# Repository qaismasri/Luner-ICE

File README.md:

<div align="center">

# Lunar-ICE Rover

**A remotely operated lunar rover that drives a simulated lunar surface and identifies rocks
by their radio, infrared, ultrasonic and magnetic signatures.**

Imperial College London · ELEC40006 Electronics Design Project 1 (EEERover) · Group 15

</div>

## About the project

The goal was to design and build, from scratch, a remotely controlled rover capable of exploring a simulated lunar surface and surveying the rocks it finds there. The rover has to be driven around large obstacles by a remote operator, park itself next to a target rock, and work out two things about it: **how old it is**, and **what type of rock it is**.

Nothing about the rock is visible from the outside. Everything the rover reports has to be recovered from four faint signals the rock emits — a radio transmission carrying its age, infrared pulses, an ultrasonic tone, and a magnetic field. Each of those needed its own sensor, its own analogue signal chain to pull a usable signal out of the noise, and its own place on the chassis.

The project ran over one term as a six-person group design exercise, and had to satisfy a handful of hard constraints:

- **Under 750 g** all-up mass
- **£60 budget** for components
- **3.3 V logic throughout** — the microcontroller's inputs are not 5 V tolerant
- Driven entirely by a **remote operator**, with no line-of-sight assumptions beyond the same Wi-Fi network

<div align="center">
<table>
<tr>
<td width="50%" align="center" valign="top">

<br><sub><b>Complete assembly</b> — both plates, radio arm and sensor arm</sub>
</td>
<td width="50%" align="center" valign="top">

<br><sub><b>Two-plate stack</b> — motors and power below, sensors above</sub>
</td>
</tr>
<tr>
<td width="50%" align="center" valign="top">

<br><sub><b>Sensor arm</b> — sweeps three sensors across the rock</sub>
</td>
<td width="50%" align="center" valign="top">

<br><sub><b>Radio arm</b> — fixed, angled down toward the rock</sub>
</td>
</tr>
</table>
</div>

> These are the Fusion 360 renders. Photographs of the built rover are the one thing this repository still lacks — see [the wanted list](docs/images/README.md#photographs-still-wanted).

<div align="right"></div>

## Contents

| Section | What you will find |
|:---|:---|
| **[About the project](#about-the-project)** | Goals, constraints and what the rover has to do |
| **[Team](#team)** | Who built it, and who did what |
| **[The sensors](#the-sensors)** | The four sensing subsystems, one picture each |
| **[Identifying a rock](#identifying-a-rock)** | How four signals become a rock type and an age |
| **[System architecture](#system-architecture)** | The two-board split and how data flows |
| **[Documentation](#documentation)** | All twelve technical chapters |
| **[Repository layout](#repository-layout)** | Where everything lives |
| **[Build and run](#build-and-run)** | Getting it onto the hardware |

For the full technical write-up — calculations, simulations, measurements and PCB files — go to **[the documentation](docs/README.md)**.

<div align="right"></div>

## Team

**Group 15** — six first-year students, with the work split by subsystem.

| Name | Main contributions |
|:---|:---|
| **Tibor Varga** | Radio circuit design and LTspice simulation |
| **Junhao Liu** | Chassis and sensor arm CAD, magnetic sensing |
| **Qais Masri** | Radio research, PCB design, movement and controller, finances |
| **Tunir Sarkar** | Infrared sensor and firmware |
| **Yangping Li** | Motor subsystem and drive integration |
| **Shivang Mehra** | Ultrasound and magnetic sensing, integration |

<div align="right"></div>

## The sensors

Four independent subsystems. The **radio** reports the rock's age; the other three combine to give its type.

<table>
<tr>
<td width="50%" align="center" valign="top">

<br><b>Radio</b> · rock age
<br><sub>120-turn ferrite coil tuned to 89&nbsp;kHz.<br>ASK carrier, UART at 600&nbsp;baud.</sub>
</td>
<td width="50%" align="center" valign="top">

<br><b>Infrared</b> · rock type
<br><sub>SFH300 phototransistor, ×100 amplifier,<br>band-pass filter, LM393 comparator.</sub>
</td>
</tr>
<tr>
<td width="50%" align="center" valign="top">

<br><b>Ultrasound</b> · rock type
<br><sub>Prowave 400SR160 receiver, two ×34 stages,<br>deliberately clipped, envelope detected.</sub>
</td>
<td width="50%" align="center" valign="top">

<br><b>Magnetic</b> · rock type
<br><sub>SEN0619 (BMM350) TMR magnetometer,<br>0.1&nbsp;µT resolution over I²C.</sub>
</td>
</tr>
</table>

Click any sensor to read its full design write-up.

<div align="right"></div>

## Identifying a rock

Each rock type maps to a unique combination of the three type-sensors:

| Rock type | Infrared | Ultrasound | Magnetic |
|:---|:---|:---|:---|
| **Basaltoid** | 547 Hz | Present | Down |
| **Gravion** | 312 Hz | Absent | Down |
| **Regolix** | 312 Hz | Present | Up |
| **Lunarite** | 547 Hz | Absent | Up |

Read as a truth table, any **two** of the three columns identify all four types. All three are measured anyway, so they cross-check one another and produce a **confidence score** — the figure that tells the operator when a reading is unreliable and should be rescanned.

The rover is driven and scanned entirely from a browser on the same Wi-Fi network, so the operator needs no special software.

<div align="center">

</div>

<div align="right"></div>

## System architecture

The rover runs on **two Adafruit Metro M0 Express boards**, split by responsibility. Board 2 does nothing but read sensors; Board 1 handles Wi-Fi, the motors and the classification. Keeping them separate means network activity can never disturb sensor timing.

```mermaid
flowchart LR
    subgraph Rock
        R["Target rock"]
    end

    subgraph B2["Board 2 — Sensing"]
        RAD["Radio<br/>89 kHz ASK"]
        IR["Infrared<br/>pulse counter"]
        US["Ultrasound<br/>40 kHz"]
        MAG["Magnetometer<br/>BMM350"]
    end

    subgraph B1["Board 1 — Control"]
        WEB["Wi-Fi web server"]
        CLS["Classification"]
        MOT["Motor driver"]
    end

    OP(["Operator<br/>browser + gamepad"])

    R --> RAD & IR & US & MAG
    RAD & IR & US & MAG --> PKT["Sensor packet @ 1 Hz"]
    PKT -->|"UART link"| B1
    WEB <-->|HTTP over Wi-Fi| OP
    CLS --> WEB
    MOT --> WHEELS["Drive motors"]
```

<div align="center">

</div>

<div align="right"></div>

## Documentation

The complete write-up — design reasoning, calculations, LTspice simulations, oscilloscope captures, CAD renders and PCB layouts — lives in [`docs/`](docs/README.md).

| # | Chapter | What it covers |
|:--|:---|:---|
| 01 | [System overview](docs/01-system-overview.md) | Mission objectives, rock types, architecture, data flow |
| 02 | [Infrared sensing](docs/02-infrared.md) | Phototransistor front-end, band-pass filtering, comparator, pulse counting |
| 03 | [Radio sensing](docs/03-radio.md) | Ferrite antenna, tuned LC, amplifier, envelope detector, Schmitt trigger, UART decode |
| 04 | [Ultrasound sensing](docs/04-ultrasound.md) | 40 kHz transducer, two-stage gain, deliberate clipping, envelope detection |
| 05 | [Magnetic field sensing](docs/05-magnetic-field.md) | Hall-effect dead end, switch to a TMR magnetometer, thresholds |
| 06 | [Mechanical design](docs/06-mechanical-design.md) | Two-plate chassis, radio arm, servo-driven sensor sweep arm |
| 07 | [Movement and control](docs/07-movement-and-control.md) | Tank steering, keyboard control, gamepad mixing, latency fix |
| 08 | [PCB design](docs/08-pcb-design.md) | Two-board split, schematics, footprints, layout rules |
| 09 | [Web interface](docs/09-web-interface.md) | Mission control page, chunked serving, scan workflow |
| 10 | [Dual-board architecture](docs/10-dual-board-architecture.md) | Why two boards, the UART link, packet format, classification |
| 11 | [Cost and bill of materials](docs/11-cost-and-bom.md) | Component spend against budget |
| 12 | [References](docs/12-references.md) | Datasheets and sources |

New to the project? Start with [chapter 01](docs/01-system-overview.md).

<div align="right"></div>

## Repository layout

```
Lunar-ICE/
├── docs/                      Technical documentation and all 71 figures
│
├── Full_Board_Code/           Flight firmware — the code that runs on the rover
│   ├── Board 1/               Wi-Fi, web server, motors, rock classification
│   └── Board 2/               All four sensors, streams readings to Board 1
│
├── Lonely_Board/              Single-board prototype (everything on one Metro M0)
│
├── sensing/                   Per-subsystem research, test firmware and PCBs
│   ├── Infrared/              IR pulse-detection test code
│   ├── radio/                 Coil calculations and radio test code
│   ├── ultrasonic/            Ultrasonic test code and design notes
│   ├── magnetic/              Magnetometer test code
│   └── PCBs/                  KiCad projects and manufacturing Gerbers
│
└── software/                  Web interface, servo tests, classification notes
    ├── Website/rover_website/ Board 1 firmware serving mission control
    └── Servo_test/            Sensor-arm servo sweep test
```

Every folder has its own README: [docs](docs/README.md) · [figures](docs/images/README.md) · [firmware](Full_Board_Code/README.md) · [prototype](Lonely_Board/README.md) · [sensing](sensing/README.md) · [software](software/README.md)

<div align="right"></div>

## Build and run

You will need [PlatformIO](https://platformio.org/install) and two Adafruit Metro M0 Express boards, one with a WINC1500 Wi-Fi shield.

```bash
cd "Full_Board_Code/Board 1"     # Wi-Fi, web interface, motors, classification
pio run --target upload

cd "Full_Board_Code/Board 2"     # sensors
pio run --target upload
```

Board 1 prints its IP address over USB serial on boot — open it in a browser on the same network to drive the rover and trigger scans.

Wiring, Wi-Fi credentials and build notes are in **[Full_Board_Code/README.md](Full_Board_Code/README.md)**.

<div align="right"></div>

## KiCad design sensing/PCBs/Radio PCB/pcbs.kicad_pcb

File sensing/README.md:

[← Repo home](../README.md) · [Technical documentation](../docs/README.md)

# Sensing

Research, circuit design, test firmware and PCB files for all four sensing subsystems on the Lunar-ICE rover.

Each subsystem detects one property of a rock and reduces it to a signal the Metro M0 can read. The full write-up for each — design reasoning, calculations, simulations and measurements — is in [`docs/`](../docs/); this folder holds the working files.

---

## Subsystems

| Subsystem | Detects | Documentation | Test firmware | Status |
|---|---|---|---|---|
| **Radio** | Rock age, via 89 kHz ASK | [docs/03-radio.md](../docs/03-radio.md) | [`radio/radio_test_code/`](radio/radio_test_code/) | ✅ Working |
| **Infrared** | Rock type, via pulse rate | [docs/02-infrared.md](../docs/02-infrared.md) | [`Infrared/ir_test_code/`](Infrared/ir_test_code/) | ✅ Working |
| **Ultrasound** | Rock type, via 40 kHz tone | [docs/04-ultrasound.md](../docs/04-ultrasound.md) | [`ultrasonic/ultrasonic_test_code/`](ultrasonic/ultrasonic_test_code/) | ✅ Working |
| **Magnetic** | Rock type, via magnet polarity | [docs/05-magnetic-field.md](../docs/05-magnetic-field.md) | [`magnetic/Magnetic_test_code/`](magnetic/Magnetic_test_code/) | ✅ Working |

---

## Folder contents

```
sensing/
├── Infrared/
│   └── ir_test_code/                  Pulse counting via hardware interrupt
├── radio/
│   ├── COIL_CALCULATIONS.md           Ferrite coil inductance and resistance working
│   ├── step1_coil_antenna.png         The wound coil
│   └── radio_test_code/               UART decode of the demodulated bitstream
├── ultrasonic/
│   ├── Ultrasonic_sensor_notes.md     Transducer, gain planning and test log
│   └── ultrasonic_test_code/          Digital-level presence detection
├── magnetic/
│   └── Magnetic_test_code/            BMM350 read over I²C
├── radio_ultrasound_magnetic/         Combined three-sensor integration test
└── PCBs/                              KiCad projects and manufacturing Gerbers
```

Each folder containing a `platformio.ini` is a standalone [PlatformIO](https://platformio.org/) project:

```bash
cd sensing/Infrared/ir_test_code
pio run --target upload
```

The **flight firmware** that actually runs on the rover is not here — it is in [`Full_Board_Code/Board 2/`](../Full_Board_Code/Board%202/), which combines all four subsystems. The projects in this folder are the per-subsystem test rigs used during development, kept because they are the quickest way to bring one sensor up in isolation when debugging.

---

## How it fits together

```mermaid
flowchart LR
    A["🪨 Rock"] --> B["Radio<br/>89 kHz ASK"]
    A --> C["Infrared<br/>312 / 547 Hz"]
    A --> D["Ultrasound<br/>40 kHz"]
    A --> E["Magnetic<br/>up / down"]

    B --> F["Board 2<br/>Metro M0"]
    C --> F
    D --> F
    E --> F

    F -->|"CSV packet @ 1 Hz over UART"| G["Board 1"]
    G --> H["Rock classification"]
```

The radio yields the rock's **age**. The other three combine to give its **type** — see [Rock classification](../docs/10-dual-board-architecture.md#107-rock-classification).

---

## PCBs

Two boards were manufactured. See [docs/08-pcb-design.md](../docs/08-pcb-design.md) for schematics, layout rules and 3D renders.

| Board | KiCad project | Gerbers |
|---|---|---|
| Radio | [`PCBs/Radio PCB/`](PCBs/Radio%20PCB/) | [`PCBs/Radio final PCB/`](PCBs/Radio%20final%20PCB/) |
| IR + ultrasound | [`PCBs/IR + ultrasound/`](PCBs/IR%20+%20ultrasound/) | [`PCBs/Infrared final pcb/`](PCBs/Infrared%20final%20pcb/) |
| Demo | [`PCBs/Demo pcb/`](PCBs/Demo%20pcb/) | [`PCBs/Final files greber/`](PCBs/Final%20files%20greber/) |

Magnetic sensing needs no PCB — the SEN0619 module outputs digitally over I²C and wires straight to the Metro.

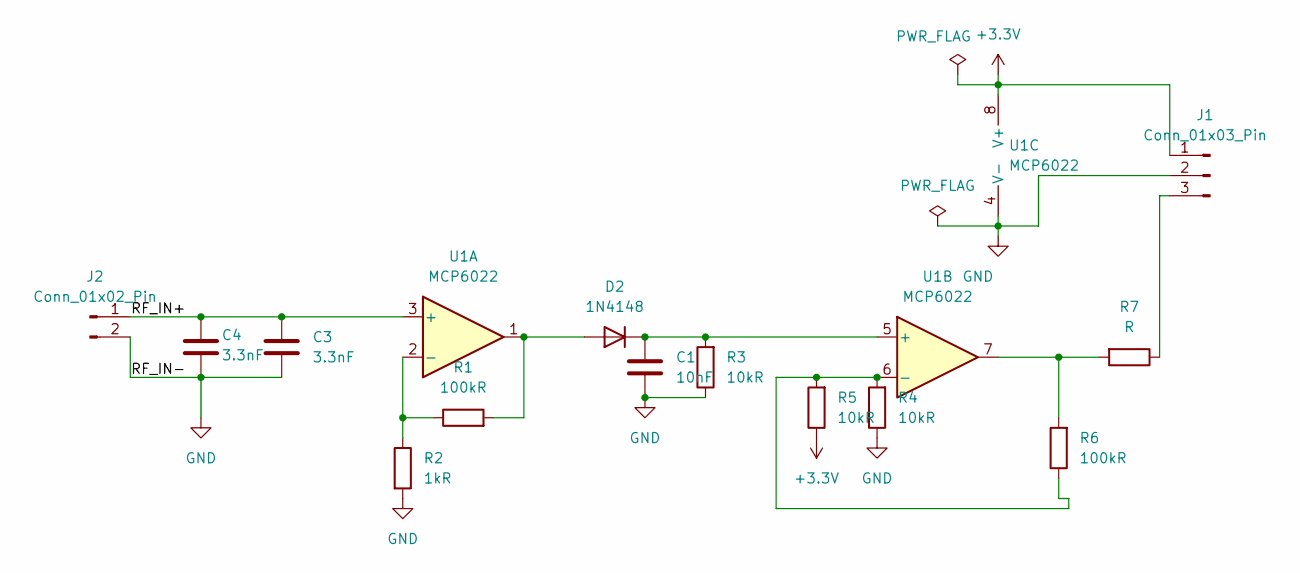
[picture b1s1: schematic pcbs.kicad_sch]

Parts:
C1: 10nF; C_Disc_D3.4mm_W2.1mm_P2.50mm
C3, C4: 3.3nF; C_Disc_D5.0mm_W2.5mm_P5.00mm
D2: 1N4148; D_DO-35_SOD27_P3.81mm_Vertical_AnodeUp
J1: Conn_01x03_Pin; PinHeader_1x03_P2.54mm_Vertical
J2: Conn_01x02_Pin; PinHeader_1x02_P2.54mm_Vertical
R1, R6: 100kR; R_Axial_DIN0207_L6.3mm_D2.5mm_P7.62mm_Horizontal
R2: 1kR; R_Axial_DIN0207_L6.3mm_D2.5mm_P7.62mm_Horizontal
R3, R4, R5: 10kR; R_Axial_DIN0207_L6.3mm_D2.5mm_P7.62mm_Horizontal
R7: R; R_Axial_DIN0207_L6.3mm_D2.5mm_P7.62mm_Horizontal
U1: MCP6022; DIP-8_W7.62mm

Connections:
+3.3V: J1.1, R5.1, U1.8 (V+)
/RF_IN+: C3.1, C4.1, J2.1, U1.3 (+)
GND: C1.2, C3.2, C4.2, J1.2, J2.2, R2.2, R3.1, R4.1, U1.4 (V-)
unnamed: D2.2 (A), R1.2, U1.1
unnamed: C1.1, D2.1 (K), R3.2, U1.5 (+)
unnamed: J1.3, R7.1
unnamed: R6.2, R7.2, U1.7
unnamed: R1.1, R2.1, U1.2 (-)
unnamed: R4.2, R5.2, R6.1, U1.6 (-)

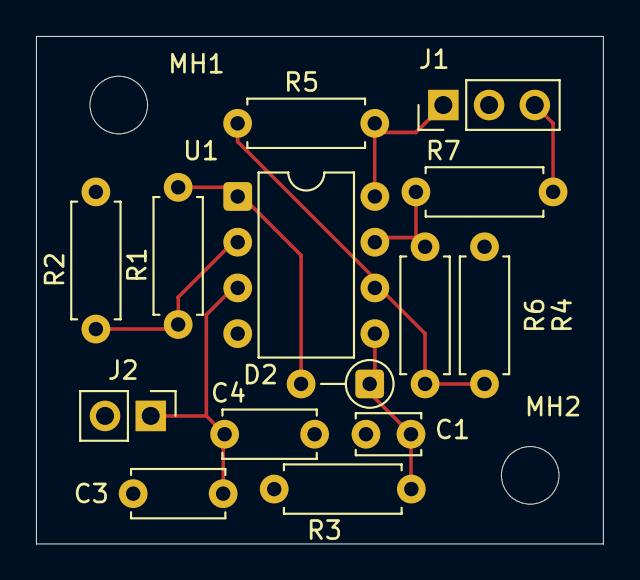
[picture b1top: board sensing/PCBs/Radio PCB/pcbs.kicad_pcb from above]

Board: 2 copper layers, 31.5 x 28.2 mm, 16 parts (0 on the bottom side), 9 nets.

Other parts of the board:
MH1, MH2: MountingHole_3.2mm_M3_DIN965

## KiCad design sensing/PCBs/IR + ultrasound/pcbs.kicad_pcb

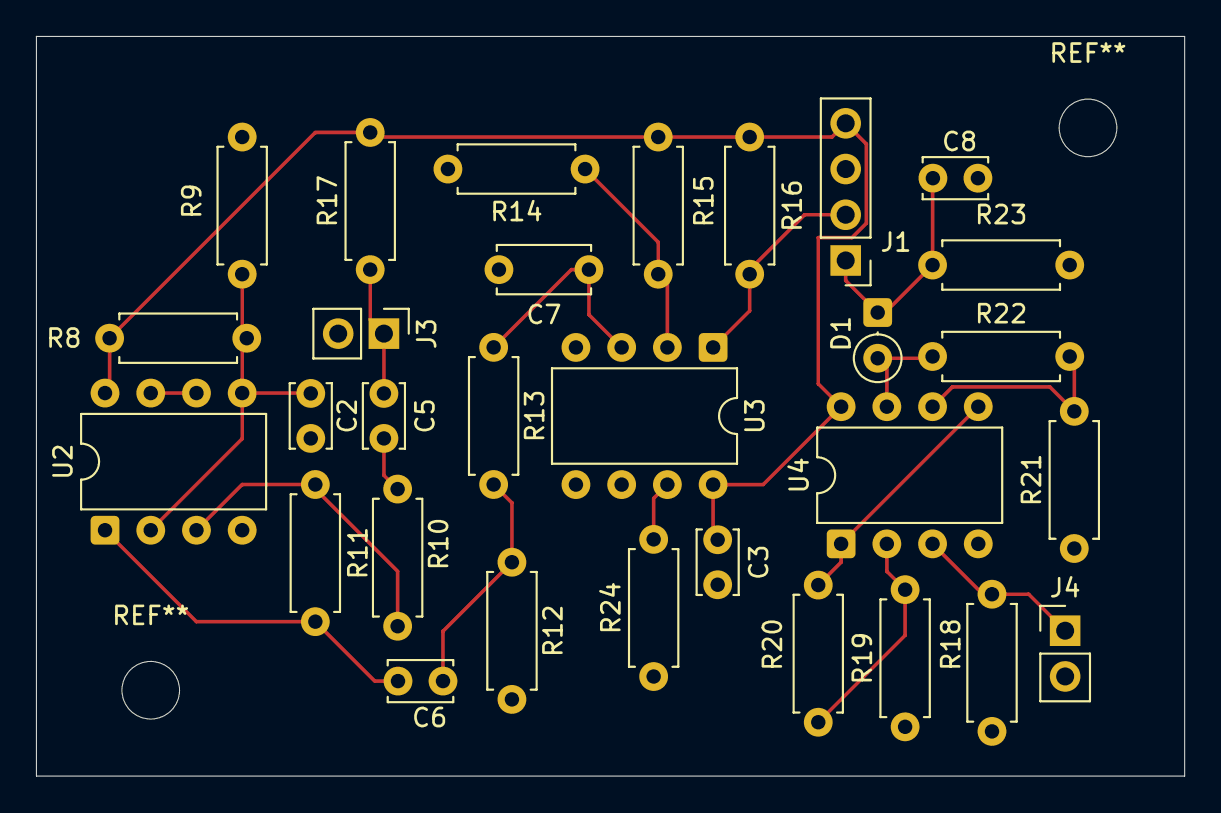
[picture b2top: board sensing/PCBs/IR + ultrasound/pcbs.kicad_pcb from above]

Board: 2 copper layers, 63.8 x 41.1 mm, 30 parts (0 on the bottom side), 19 nets.

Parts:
C2, C3, C5, C6, C8: 100nF; C_Disc_D3.4mm_W2.1mm_P2.50mm
C7: 3.3nF; C_Disc_D5.0mm_W2.5mm_P5.00mm
D1: 1N4148; D_DO-35_SOD27_P2.54mm_Vertical_CathodeUp
J1: i/o; PinHeader_1x04_P2.54mm_Vertical
J3: Infra_in; PinHeader_1x02_P2.54mm_Vertical
J4: Ultra_in; PinHeader_1x02_P2.54mm_Vertical
R8, R9, R12, R19, R21, R23, R24: 10kR; R_Axial_DIN0207_L6.3mm_D2.5mm_P7.62mm_Horizontal
R10, R13, R14, R16: 1kR; R_Axial_DIN0207_L6.3mm_D2.5mm_P7.62mm_Horizontal
R11, R17: 100kR; R_Axial_DIN0207_L6.3mm_D2.5mm_P7.62mm_Horizontal
R15: 27kR; R_Axial_DIN0207_L6.3mm_D2.5mm_P7.62mm_Horizontal
R18: 39kR; R_Axial_DIN0207_L6.3mm_D2.5mm_P7.62mm_Horizontal
R20, R22: 330kR; R_Axial_DIN0207_L6.3mm_D2.5mm_P7.62mm_Horizontal
U2, U4: MCP6022; DIP-8_W7.62mm
U3: LM393; DIP-8_W7.62mm

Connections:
+3.3V: C3.1, J1.4, R8.2, R15.1, R16.1, R17.2, U2.8 (V+), U3.8 (V+), U4.8 (V+)
/Vg: C2.1, R8.1, R9.2, U2.2 (-), U2.5 (+)
GND: C2.2, C3.2, C7.2, C8.1, J1.3, J3.2, J4.2, R9.1, R12.1, R14.2, R18.2, R19.1, R21.1, R23.1, R24.1, U2.4 (V-), U3.4 (V-), U3.5 (+), U3.6 (-), U4.4 (V-)
unnamed: C5.2, R10.1
unnamed: C6.1, R11.2, U2.1
unnamed: C6.2, R12.2, R13.1
unnamed: D1.2 (A), R22.1, U4.7
unnamed: C8.2, D1.1 (K), J1.1, R23.2
unnamed: J1.2, R16.2, U3.1
unnamed: C5.1, J3.1, R17.1
unnamed: J4.1, R18.1, U4.3 (+)
unnamed: R24.2, U3.7
unnamed: R10.2, R11.1, U2.3 (+)
unnamed: U2.6 (-), U2.7
unnamed: C7.1, R13.2, U3.3 (+)
unnamed: R14.1, R15.2, U3.2 (-)
unnamed: R19.2, R20.2, U4.2 (-)
unnamed: R20.1, U4.1, U4.5 (+)
unnamed: R21.2, R22.2, U4.6 (-)

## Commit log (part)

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2026-05-13 Add deadlines tracking file for team task management
2026-05-13 Update team members and their deadlines
2026-05-13 Fix typo in name from 'Yangpin' to 'Yangping'
2026-05-13 Add CODEOWNERS file for repository ownership
2026-05-13 Enhance DEADLINES.md with Task 1 instructions
    Added detailed instructions for Task 1 and updated the deadlines section.
2026-05-13 Update Junhao's task to Infrared with Tunir
2026-05-13 Add Ultrasonic Sensor Notes documentation
2026-05-13 Add detailed notes on current ultrasonic receiver component and signal requirements
2026-05-14 Add README for Radio Subsystem — Age Detection
    Added detailed documentation for the Radio Subsystem, including signal processing steps, build notes, component research, and testing checklist.
2026-05-14 Add README for sensing subsystems on Luner-ICE rover
2026-05-14 Remove placeholder text for photos in README
    Updated README.md to remove placeholder text for photos.
2026-05-18 Add detailed ultrasonic sensor notes including transducer and op-amp requirements, signal flow, and test results
2026-05-18 Add initial project structure for ultrasonic sensor testing, including configuration files, README documentation, and main code implementation
2026-05-18 Add component orders documentation
2026-05-19 Add initial implementation for ultrasonic sensor testing, including configuration files, README documentation, and main code
2026-05-21 website 'design' made
2026-05-24 Update purchases.md with new orders and components
    Added new orders with components and suppliers for 21/05/2026 and 22/05/2026.
2026-05-29 Add build artifacts and configuration files for Adafruit Metro M0
    - Created new binary files for various FrameworkArduino components including IPAddress, Print, Reset, SERCOM, Stream, Tone, and USB functionalities.
    - Added object files for DFRobot_BMM350 library and its components.
    - Generated firmware binaries (firmware.bin, firmware.elf) for the project.
    - Included idedata.json for IDE integration and project settings.
    - Updated c_cpp_properties.json and launch.json for VSCode debugging support.
    - Added integrity.dat for library dependency tracking.
2026-05-31 Added coil information for radio
2026-05-31 Rename step1_coil_antenna.jpeg to step1_coil_antenna.jpg
2026-05-31 Changed website code to include sense button and removed hardcoded data
2026-05-31 Added Radio test code Added Radio + Ultrasound + Magnetic test code Added website + RUM code.
2026-06-05 Add initial project structure and configuration for Board 2
    - Created README files for test, include, and lib directories to provide guidance on usage.
    - Added .gitignore to exclude build artifacts and IDE configuration files.
    - Configured VSCode settings and extensions for PlatformIO development.
    - Implemented platformio.ini for Board 2 with dependencies and board configuration.
    - Developed main application logic in src/main.cpp for sensor data handling and communication with Board 1.
    - Updated WiFi credentials in Lonely_Board and rover_website projects for network connectivity.
2026-06-05 Add configuration files for PlatformIO in multiple directories
2026-06-11 Added the IR sensor code to detect pulses
2026-06-11 Updating costs
2026-06-13 Add PCB design files for Demo, IR+ultrasound, and Radio boards
2026-06-15 savebeforedisaster
2026-06-15 changes to website (pretty much final changes)
2026-06-16 Finalised Board code
